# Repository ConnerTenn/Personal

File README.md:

This repository is outdated. 
Projects will now be located in their own repository and will no longer be updated here.
This repository is being kept for commit and file history.

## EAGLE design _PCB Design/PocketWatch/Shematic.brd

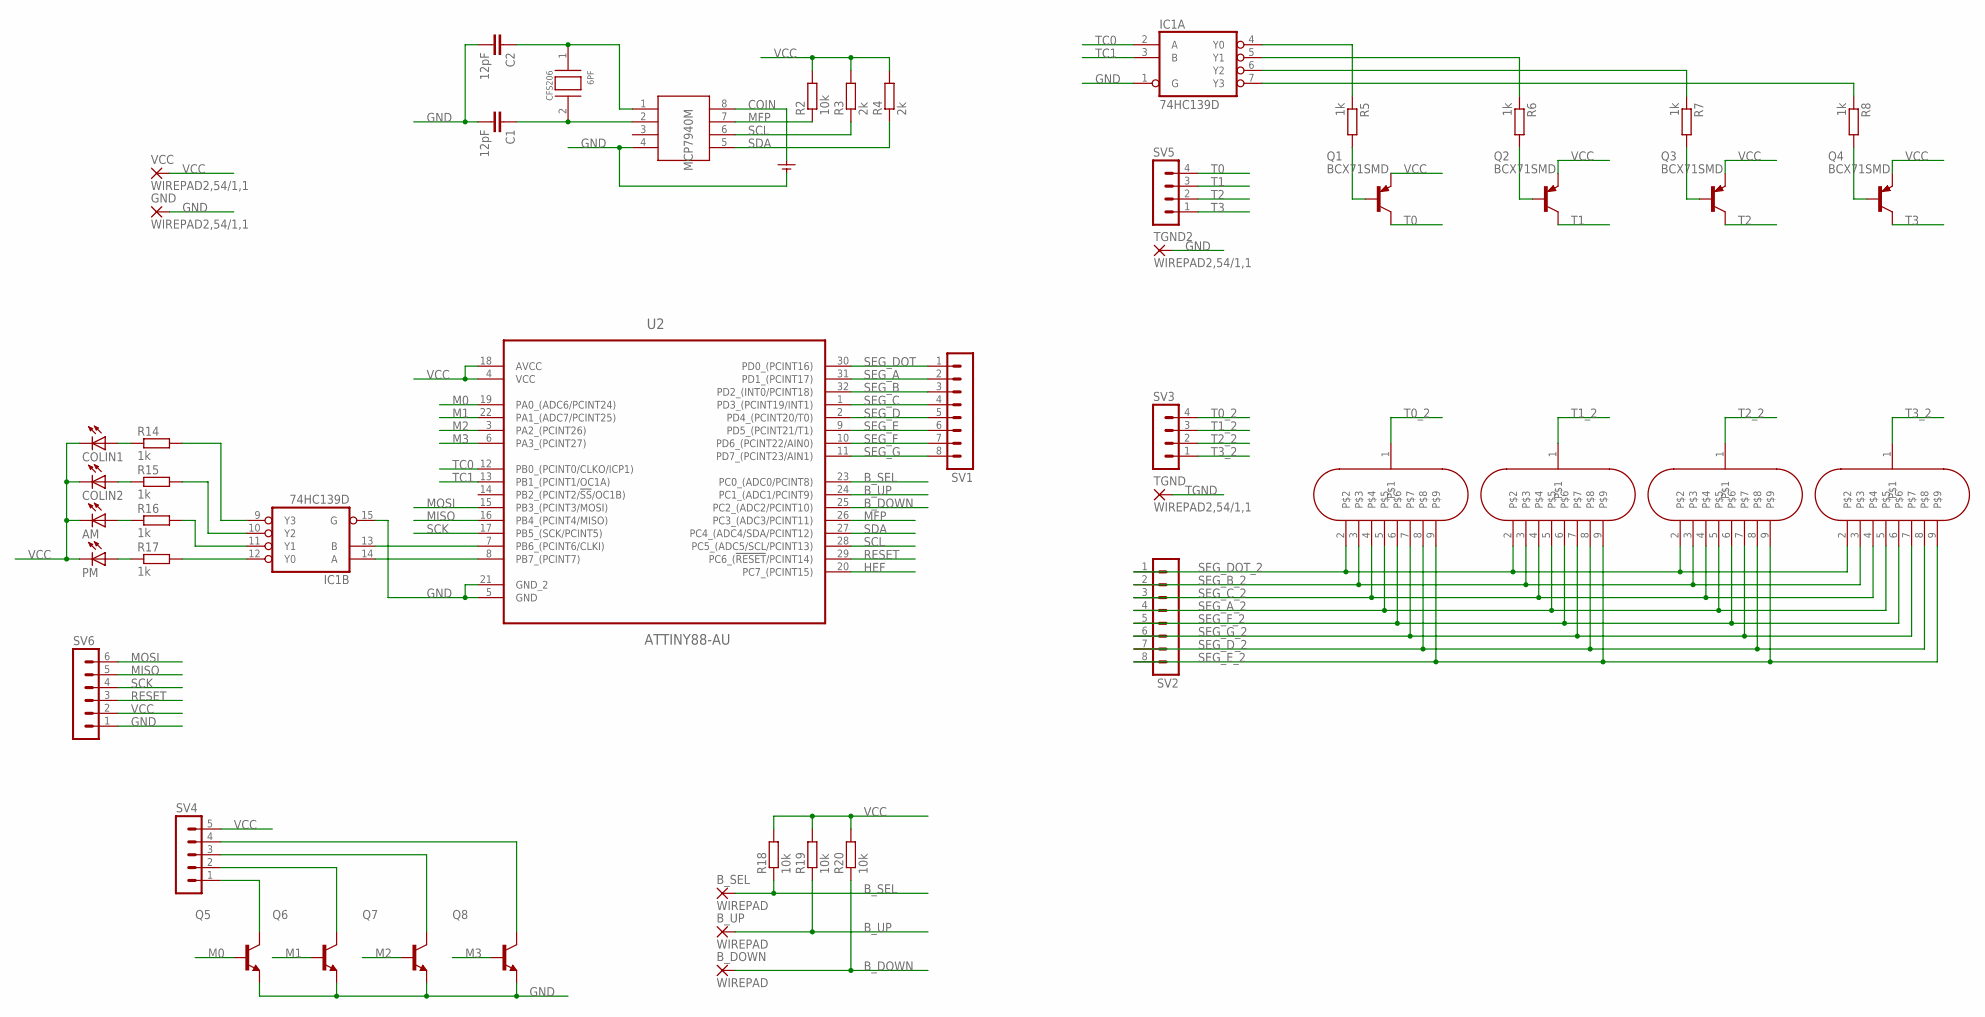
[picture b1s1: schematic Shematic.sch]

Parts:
6PF: CFS206
AM: LED_ELD260; LED_LD260
B_DOWN: WIREPAD; 2,54/1,1
B_SEL: WIREPAD; 2,54/1,1
B_UP: WIREPAD; 2,54/1,1
C1, C2: 12pF; C1206
COLIN1, COLIN2: LED_ELD260; LED_LD260
GND: WIREPAD2,54/1,1; 2,54/1,1
IC1: 74HC139D; SO16
MCP7940M: SOIC-8
PM: LED_ELD260; LED_LD260
Q1, Q2, Q3, Q4: BCX71SMD; SOT23
Q5, Q6, Q7, Q8: BCX70SMD; SOT23
R2, R18, R19, R20: 10k; R1206
R3, R4: 2k; R1206
R5, R6, R7, R8, R14, R15, R16, R17: 1k; R1206
SV1, SV2: MA08-1
SV3, SV5: MA04-1
SV4: MA05-1
SV6: MA06-1
TGND, TGND2: WIREPAD2,54/1,1; 2,54/1,1
TUBE0, TUBE1, TUBE2, TUBE3: IV-9
U2: ATTINY88-AU; QFP80P900X900X120-32N
U$5: COIN
VCC: WIREPAD2,54/1,1; 2,54/1,1

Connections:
B_DOWN: B_DOWN.1, R20.1, U2.25 (PC2_(ADC2/PCINT10))
B_SEL: B_SEL.1, R18.1, U2.23 (PC0_(ADC0/PCINT8))
B_UP: B_UP.1, R19.1, U2.24 (PC1_(ADC1/PCINT9))
COIN: MCP7940M.8, U$5.V+
GND: C1.2, C2.2, GND.1, IC1.1 (G), IC1.8 (GND), IC1.15 (G), MCP7940M.4, Q5.2 (E), Q6.2 (E), Q7.2 (E), Q8.2 (E), SV6.1, TGND2.1, U2.5 (GND), U2.21 (GND_2), U$5.V-
HEF: U2.20 (PC7_(PCINT15))
M0: Q5.1 (B), U2.19 (PA0_(ADC6/PCINT24))
M1: Q6.1 (B), U2.22 (PA1_(ADC7/PCINT25))
M2: Q7.1 (B), U2.3 (PA2_(PCINT26))
M3: Q8.1 (B), U2.6 (PA3_(PCINT27))
MFP: MCP7940M.7, R2.1, U2.26 (PC3_(ADC3/PCINT11))
MISO: SV6.5, U2.16 (PB4_(PCINT4/MISO))
MOSI: SV6.6, U2.15 (PB3_(PCINT3/MOSI))
unnamed: Q4.1 (B), R8.2
unnamed: Q3.1 (B), R7.2
unnamed: Q2.1 (B), R6.2
unnamed: 6PF.2, C1.1, MCP7940M.2
unnamed: Q1.1 (B), R5.2
unnamed: 6PF.1, C2.1, MCP7940M.1
unnamed: COLIN1.A, R14.1
unnamed: IC1.4 (Y0), R5.1
unnamed: COLIN2.A, R15.1
unnamed: IC1.5 (Y1), R6.1
unnamed: IC1.6 (Y2), R7.1
unnamed: AM.A, R16.1
unnamed: IC1.7 (Y3), R8.1
unnamed: PM.A, R17.1
unnamed: IC1.12 (Y0), R17.2
unnamed: IC1.11 (Y1), R16.2
unnamed: IC1.10 (Y2), R15.2
unnamed: IC1.9 (Y3), R14.2
unnamed: Q5.3 (C), SV4.1
unnamed: Q6.3 (C), SV4.2
unnamed: Q7.3 (C), SV4.3
unnamed: Q8.3 (C), SV4.4
unnamed: IC1.13 (B), U2.7 (PB6_(PCINT6/CLKI))
unnamed: IC1.14 (A), U2.8 (PB7_(PCINT7))
RESET: SV6.3, U2.29 (PC6_(!RESET!/PCINT14))
SCK: SV6.4, U2.17 (PB5_(SCK/PCINT5))
SCL: MCP7940M.6, R3.1, U2.28 (PC5_(ADC5/SCL/PCINT13))
SDA: MCP7940M.5, R4.1, U2.27 (PC4_(ADC4/SDA/PCINT12))
SEG_A: SV1.2, U2.31 (PD1_(PCINT17))
SEG_A_2: SV2.4, TUBE0.5, TUBE1.5, TUBE2.5, TUBE3.5
SEG_B: SV1.3, U2.32 (PD2_(INT0/PCINT18))
SEG_B_2: SV2.2, TUBE0.3, TUBE1.3, TUBE2.3, TUBE3.3
SEG_C: SV1.4, U2.1 (PD3_(PCINT19/INT1))
SEG_C_2: SV2.3, TUBE0.4, TUBE1.4, TUBE2.4, TUBE3.4
SEG_D: SV1.5, U2.2 (PD4_(PCINT20/T0))
SEG_DOT: SV1.1, U2.30 (PD0_(PCINT16))
SEG_DOT_2: SV2.1, TUBE0.2, TUBE1.2, TUBE2.2, TUBE3.2
SEG_D_2: SV2.7, TUBE0.8, TUBE1.8, TUBE2.8, TUBE3.8
SEG_E: SV1.6, U2.9 (PD5_(PCINT21/T1))
SEG_E_2: SV2.8, TUBE0.9, TUBE1.9, TUBE2.9, TUBE3.9
SEG_F: SV1.7, U2.10 (PD6_(PCINT22/AIN0))
SEG_F_2: SV2.5, TUBE0.6, TUBE1.6, TUBE2.6, TUBE3.6
SEG_G: SV1.8, U2.11 (PD7_(PCINT23/AIN1))
SEG_G_2: SV2.6, TUBE0.7, TUBE1.7, TUBE2.7, TUBE3.7
T0: Q1.3 (C), SV5.4
T0_2: SV3.4, TUBE0.1
T1: Q2.3 (C), SV5.3
T1_2: SV3.3, TUBE1.1
T2: Q3.3 (C), SV5.2
T2_2: SV3.2, TUBE2.1
T3: Q4.3 (C), SV5.1
T3_2: SV3.1, TUBE3.1
TC0: IC1.2 (A), U2.12 (PB0_(PCINT0/CLKO/ICP1))
TC1: IC1.3 (B), U2.13 (PB1_(PCINT1/OC1A))
TGND: TGND.1
VCC: AM.K (C), COLIN1.K (C), COLIN2.K (C), IC1.16 (VCC), PM.K (C), Q1.2 (E), Q2.2 (E), Q3.2 (E), Q4.2 (E), R2.2, R3.2, R4.2, R18.2, R19.2, R20.2, SV4.5, SV6.2, U2.4 (VCC), U2.18 (AVCC), VCC.1

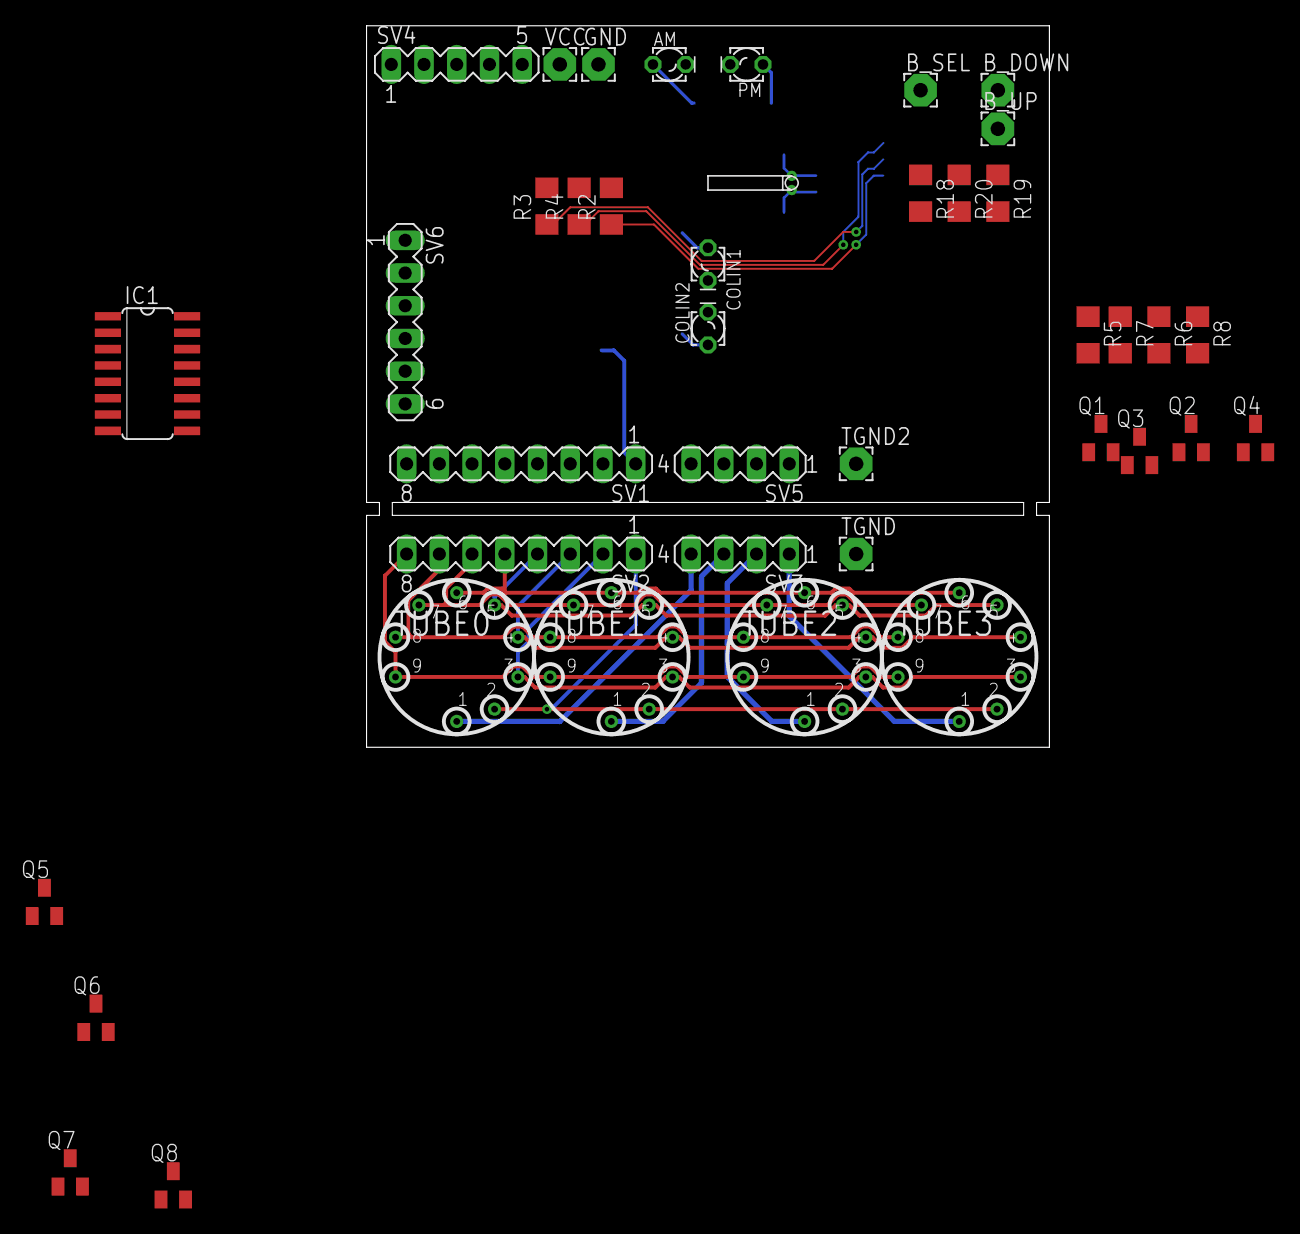
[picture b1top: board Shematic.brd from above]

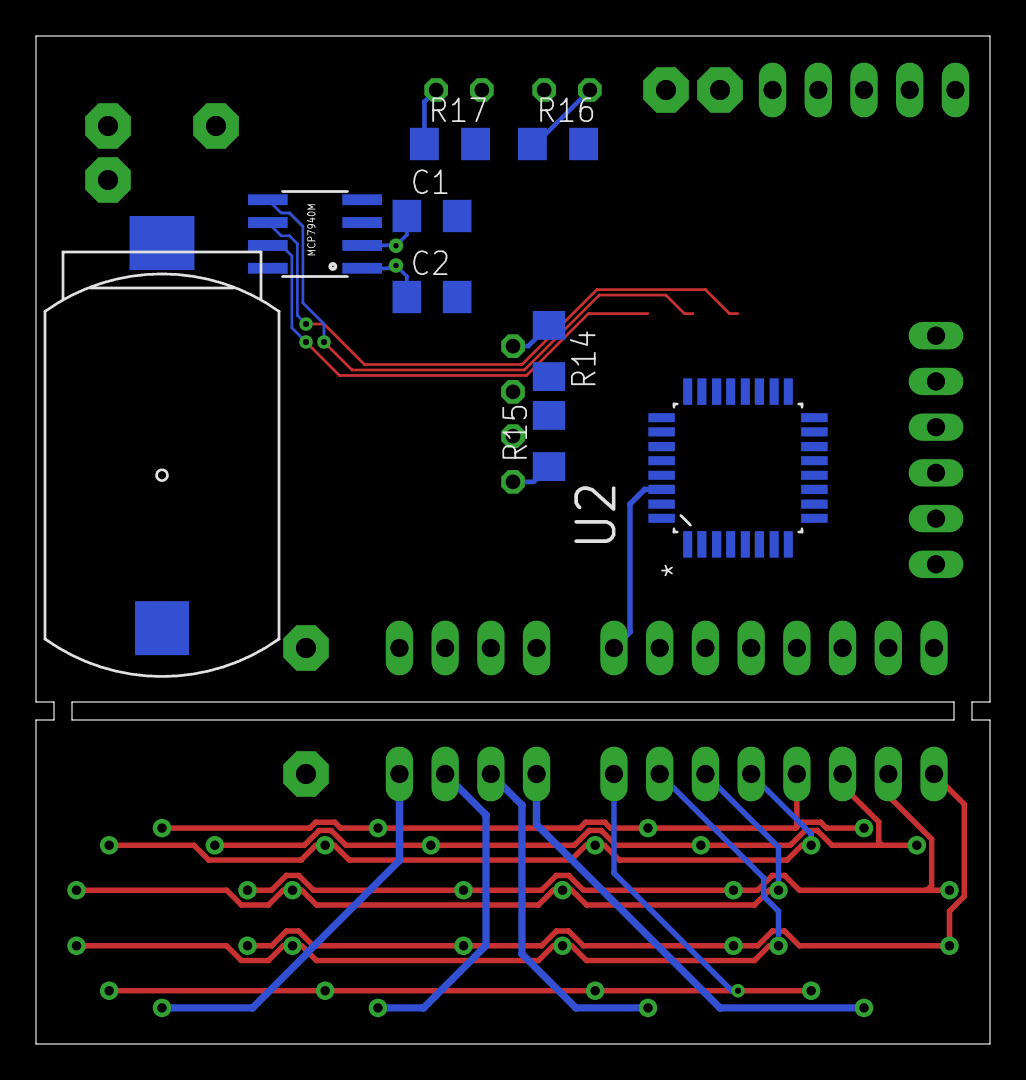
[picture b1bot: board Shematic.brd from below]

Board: 2 copper layers, 53.0 x 56.0 mm, 50 parts (9 on the bottom side), 67 nets.

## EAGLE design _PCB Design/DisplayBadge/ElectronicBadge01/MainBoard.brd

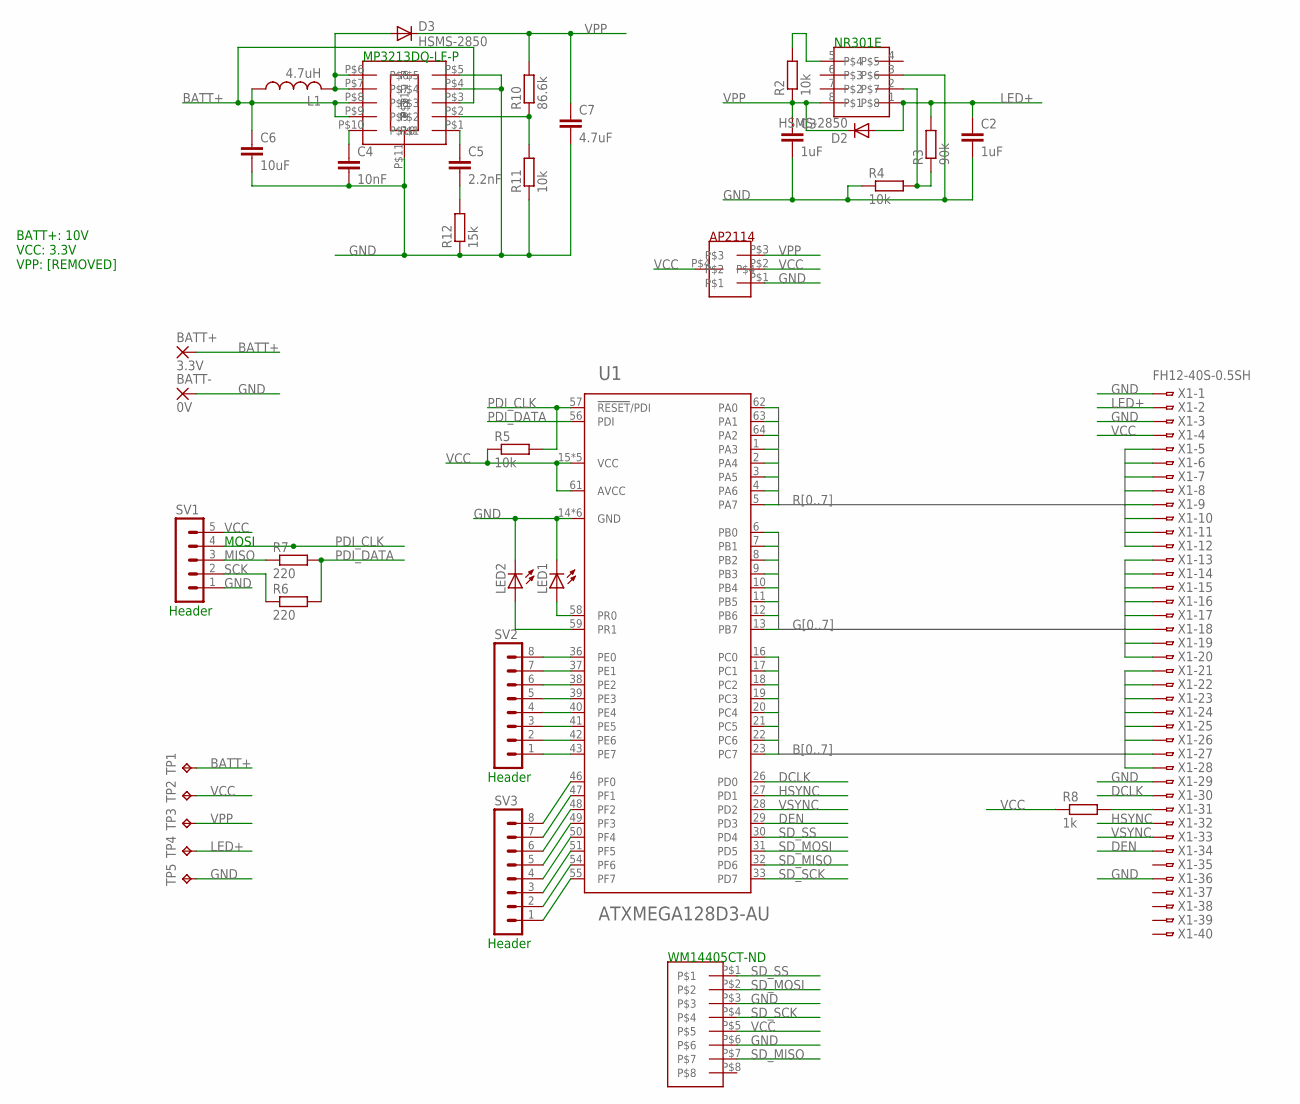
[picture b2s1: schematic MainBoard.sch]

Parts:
BATT+: 3.3V; 2,54/1,1
BATT-: 0V; 2,54/1,1
C2, C3: 1uF; C0402
C4: 10nF; C0402
C5: 2.2nF; C0402
C6: 10uF; C0402
C7: 4.7uF; C0402
D2, D3: HSMS-2850; SOT23
L1: 4.7uH; L3225M
LED1, LED2: LED_ESML0603; LED_SML0603
R2, R4, R5, R11: 10k; R0402
R3: 90k; R0402
R6, R7: 220; R0402
R8: 1k; R0402
R10: 86.6k; R0402
R12: 15k; R0402
SV1: MA05-1
SV2, SV3: MA08-1
TP1, TP2, TP3, TP4, TP5: TPPAD1-17; P1-17
U1: ATXMEGA128D3-AU; TQFP-64A-64
U$1: SOIC-8
U$2: AP2114H; SOT233
U$3: MICROSD
U$4: QFN-10
X1: FH12-40S-0.5SH

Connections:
B0: U1.16 (PC0), X1.21
B1: U1.17 (PC1), X1.22
B2: U1.18 (PC2), X1.23
B3: U1.19 (PC3), X1.24
B4: U1.20 (PC4), X1.25
B5: U1.21 (PC5), X1.26
B6: U1.22 (PC6), X1.27
B7: U1.23 (PC7), X1.28
BATT+: BATT+.1, C6.1, L1.1, TP1.TP, U$4.P$3, U$4.P$8, U$4.P$9
DCLK: U1.26 (PD0), X1.30
DEN: U1.29 (PD3), X1.34
G0: U1.6 (PB0), X1.13
G1: U1.7 (PB1), X1.14
G2: U1.8 (PB2), X1.15
G3: U1.9 (PB3), X1.16
G4: U1.10 (PB4), X1.17
G5: U1.11 (PB5), X1.18
G6: U1.12 (PB6), X1.19
G7: U1.13 (PB7), X1.20
GND: BATT-.1, C2.2, C3.2, C4.2, C6.2, C7.2, LED1.C, LED2.C, R4.1, R11.1, R12.1, SV1.1, TP5.TP, U1.14 (GND), U1.24 (GND), U1.34 (GND), U1.44 (GND), U1.52 (GND), U1.60 (GND), U$1.3, U$2.P$1, U$3.P$3, U$3.P$6, U$4.P$4, U$4.P$5, U$4.P$11, X1.1, X1.3, X1.29, X1.36
HSYNC: U1.27 (PD1), X1.32
LED+: C2.1, D2.1 (A), R3.2, TP4.TP, U$1.1, X1.2
MISO: R7.1, SV1.3
unnamed: R2.2, U$1.5
unnamed: R3.1, R4.2, U$1.2
unnamed: SV2.8, U1.36 (PE0)
unnamed: SV2.7, U1.37 (PE1)
unnamed: SV2.6, U1.38 (PE2)
unnamed: SV2.5, U1.39 (PE3)
unnamed: SV2.4, U1.40 (PE4)
unnamed: SV2.3, U1.41 (PE5)
unnamed: SV2.2, U1.42 (PE6)
unnamed: SV2.1, U1.43 (PE7)
unnamed: LED1.A, U1.58 (PR0)
unnamed: LED2.A, U1.59 (PR1)
unnamed: D3.1 (A), L1.2, U$4.P$6, U$4.P$7
unnamed: R8.2, X1.31
unnamed: SV3.8, U1.46 (PF0)
unnamed: SV3.7, U1.47 (PF1)
unnamed: SV3.6, U1.48 (PF2)
unnamed: SV3.5, U1.49 (PF3)
unnamed: SV3.4, U1.50 (PF4)
unnamed: SV3.3, U1.51 (PF5)
unnamed: SV3.2, U1.54 (PF6)
unnamed: SV3.1, U1.55 (PF7)
unnamed: C4.1, U$4.P$10
unnamed: R10.1, R11.2, U$4.P$2
unnamed: C5.1, U$4.P$1
unnamed: C5.2, R12.2
PDI_CLK: R5.2, SV1.4, U1.57 (!RESET!/PDI)
PDI_DATA: R6.2, R7.2, U1.56 (PDI)
R0: U1.62 (PA0), X1.5
R1: U1.63 (PA1), X1.6
R2: U1.64 (PA2), X1.7
R3: U1.1 (PA3), X1.8
R4: U1.2 (PA4), X1.9
R5: U1.3 (PA5), X1.10
R6: U1.4 (PA6), X1.11
R7: U1.5 (PA7), X1.12
SCK: R6.1, SV1.2
SD_MISO: U1.32 (PD6), U$3.P$7
SD_MOSI: U1.31 (PD5), U$3.P$2
SD_SCK: U1.33 (PD7), U$3.P$4
SD_SS: U1.30 (PD4), U$3.P$1
VCC: R5.1, R8.1, SV1.5, TP2.TP, U1.15 (VCC), U1.25 (VCC), U1.35 (VCC), U1.45 (VCC), U1.53 (VCC), U1.61 (AVCC), U$2.P$2, U$2.P$4, U$3.P$5, X1.4
VPP: C3.1, C7.1, D2.3 (C), D3.3 (C), R2.1, R10.2, TP3.TP, U$1.8, U$2.P$3
VSYNC: U1.28 (PD2), X1.33

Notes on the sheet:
Header
WM14405CT-ND
NR301E
MP3213DQ-LF-P
MOSI
BATT+: 10V VCC: 3.3V VPP: [REMOVED]

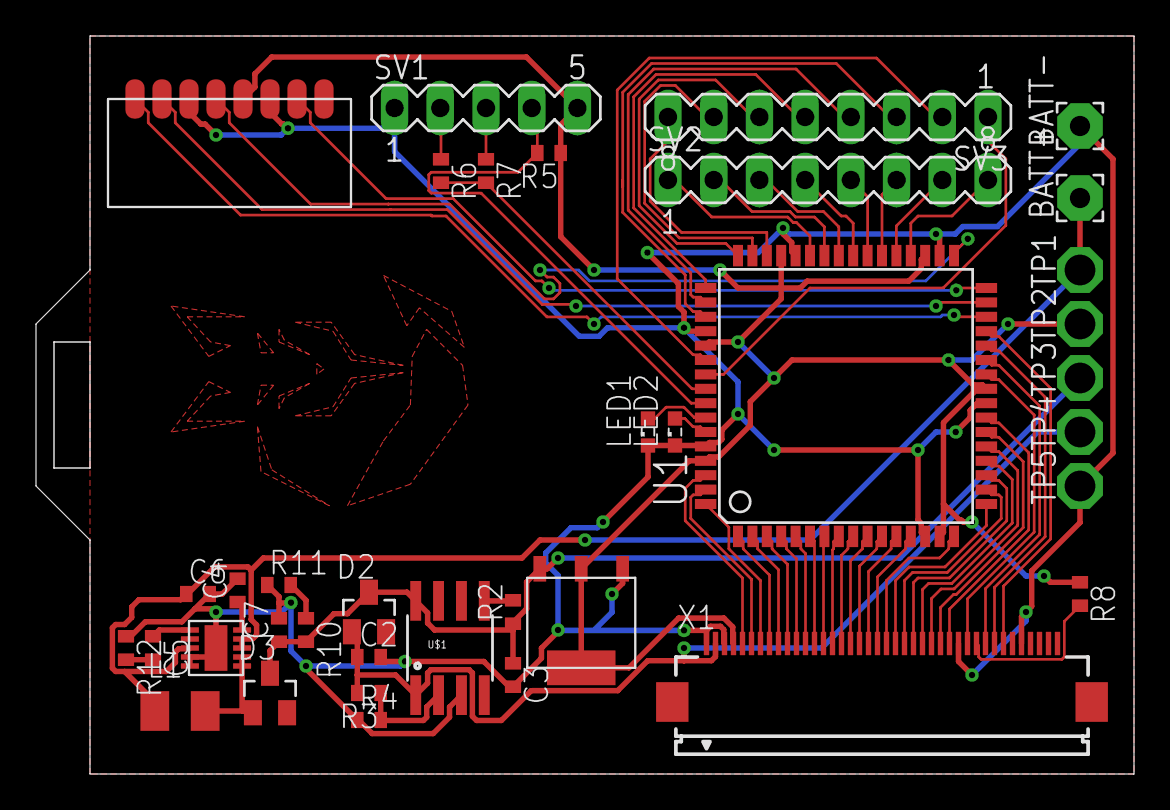
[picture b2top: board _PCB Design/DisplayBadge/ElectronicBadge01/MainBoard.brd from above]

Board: 2 copper layers, 61.0 x 41.0 mm, 37 parts (0 on the bottom side), 67 nets.

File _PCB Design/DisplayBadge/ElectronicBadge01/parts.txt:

Partlist

Exported from MainBoard.sch at 2017-10-12 2:10 AM

EAGLE Version 8.3.2 Copyright (c) 1988-2017 Autodesk, Inc.

Assembly variant: 

Part     Value          Device         Package        Library         Sheet

~ BATT+    3.3V           2,54/1,1       2,54/1,1       wirepad         1
~ BATT-    0V             2,54/1,1       2,54/1,1       wirepad         1
# C2       1uF            CC0402         C0402          eagle-ltspice   1
# C3       1uF            CC0402         C0402          eagle-ltspice   1
# C4       10nF           CC0402         C0402          eagle-ltspice   1
C5       2.2nF          CC0402         C0402          eagle-ltspice   1
# C6       10uF           CC0402         C0402          eagle-ltspice   1
# C7       4.7uF          CC0402         C0402          eagle-ltspice   1
# D2       HSMS-2850      HSMS-2850      SOT23          avago           1
# D3       HSMS-2850      HSMS-2850      SOT23          avago           1
# L1       4.7uH          L-USL3225M     L3225M         resistor        1
# LED1                    LED_ESML0603   LED_SML0603    eagle-ltspice   1
# LED2                    LED_ESML0603   LED_SML0603    eagle-ltspice   1
# R2       10k            RR0402         R0402          eagle-ltspice   1
# R3       90k            RR0402         R0402          eagle-ltspice   1
# R4       10k            RR0402         R0402          eagle-ltspice   1
# R5       10k            RR0402         R0402          eagle-ltspice   1
# R6       220            RR0402         R0402          eagle-ltspice   1
# R7       220            RR0402         R0402          eagle-ltspice   1
# R8       1k             RR0402         R0402          eagle-ltspice   1
# R10      86.6k          RR0402         R0402          eagle-ltspice   1
# R11      10k            RR0402         R0402          eagle-ltspice   1
# R12      15k            RR0402         R0402          eagle-ltspice   1
~ SV1                     MA05-1         MA05-1         con-lstb        1
~ SV2                     MA08-1         MA08-1         con-lstb        1
~ SV3                     MA08-1         MA08-1         con-lstb        1
~ TP1      TPPAD1-17      TPPAD1-17      P1-17          testpad         1
~ TP2      TPPAD1-17      TPPAD1-17      P1-17          testpad         1
~ TP3      TPPAD1-17      TPPAD1-17      P1-17          testpad         1
~ TP4      TPPAD1-17      TPPAD1-17      P1-17          testpad         1
~ TP5      TPPAD1-17      TPPAD1-17      P1-17          testpad         1
# U$1      SOIC-8         SOIC-8         SOIC-8         smd-footprints  1
# U$2      AP2114H        AP2114H        SOT233         ElectronicBadge 1
# U$3      MICROSD        MICROSD        MICROSD        ElectronicBadge 1
# U$4      QFN-10         QFN-10         QFN-10         smd-footprints  1
# U1       ATXMEGA64D3-AU ATXMEGA64D3-AU TQFP-64A-64    atmel-xmega     1
# X1       FH12-40S-0.5SH FH12-40S-0.5SH FH12-40S-0.5SH con-hirose      1

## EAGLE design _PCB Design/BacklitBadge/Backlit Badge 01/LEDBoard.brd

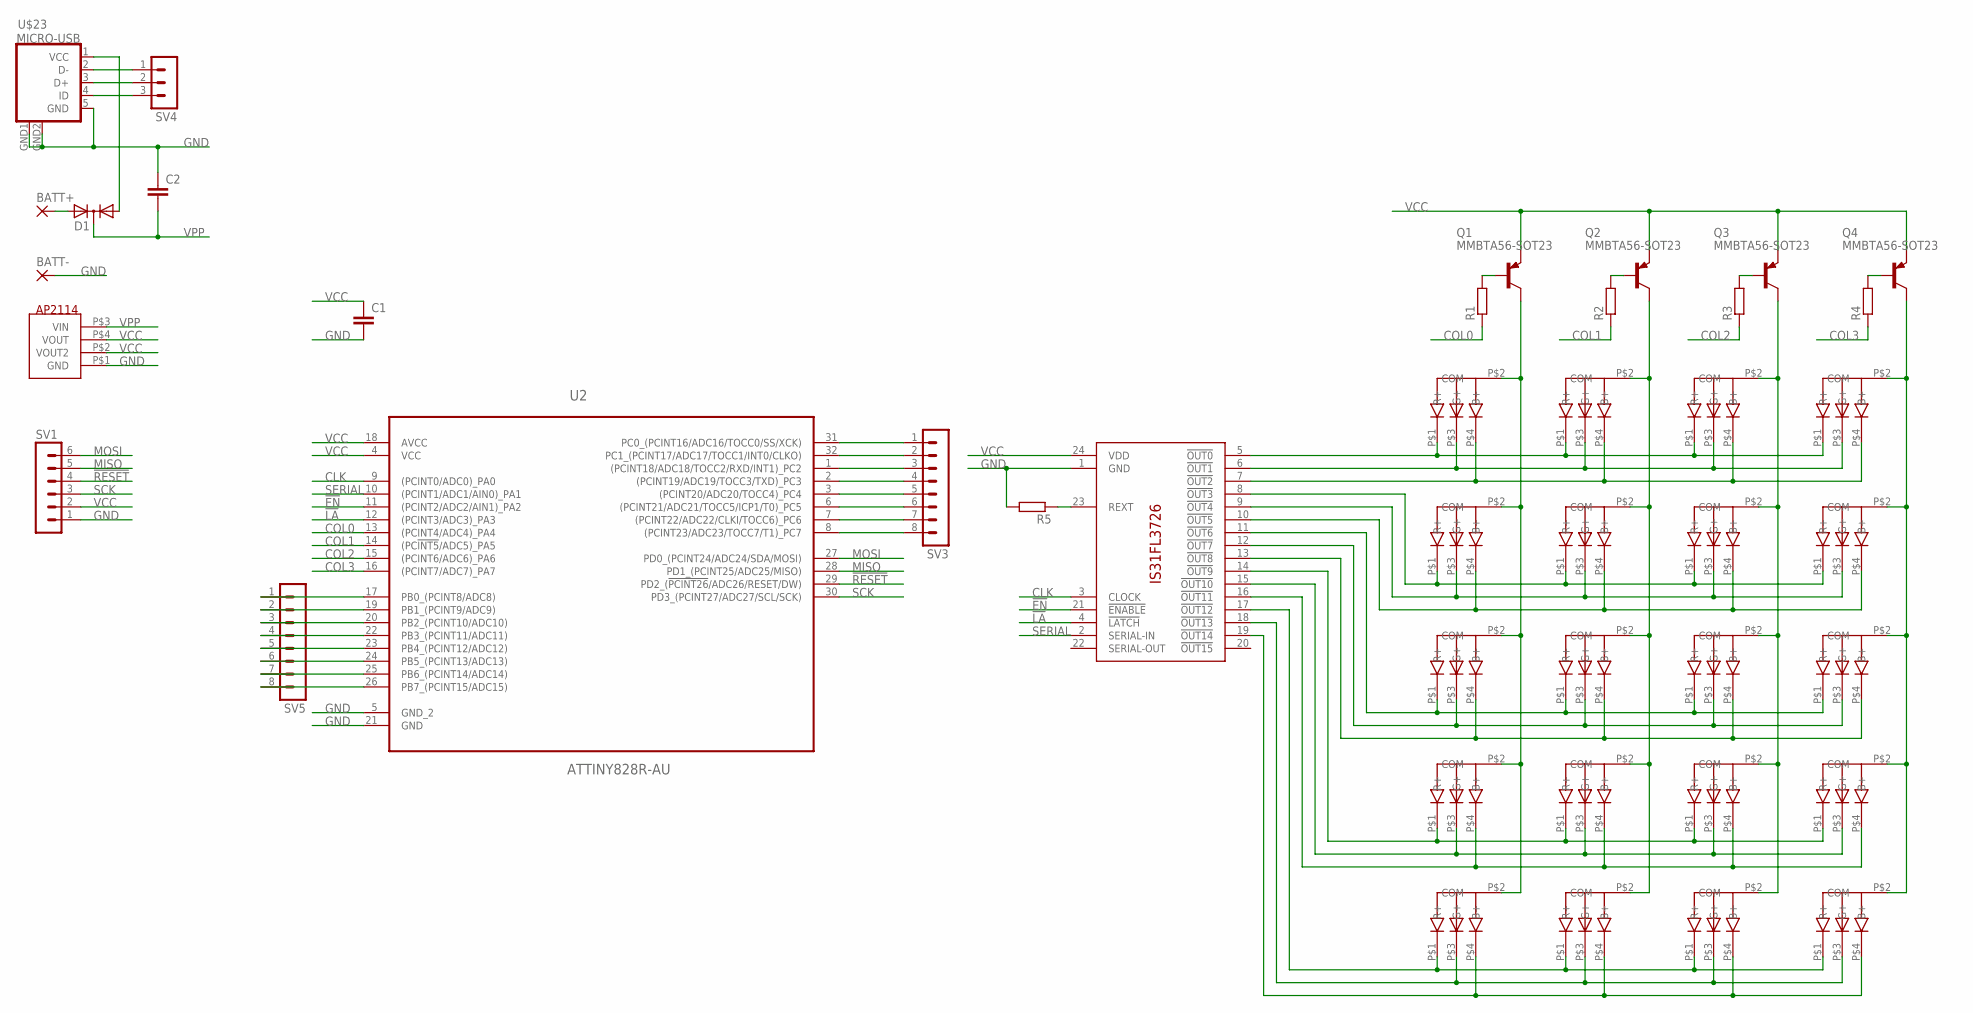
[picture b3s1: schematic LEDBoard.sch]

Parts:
BATT+: 2,54/1,1
BATT-: 2,54/1,1
C1, C2: CC1206; C1206
D1: DIODE-2AC|CASOT23; SOT23
Q1, Q2, Q3, Q4: MMBTA56-SOT23; SOT23
R1, R2, R3, R4, R5: RR1206; R1206
SV1: MA06-1
SV3, SV5: MA08-1
SV4: MA03-1
U2: ATTINY828R-AU; QFP80P900X900X120-32N
U$1: IS31FL3726; TSSOP-24
U$2: AP2114H; SOT233
U$3, U$4, U$5, U$6, U$7, U$8, U$9, U$10, U$11, U$12, U$13, U$14, U$15, U$16, U$17, U$18, U$19, U$20, U$21, U$22: 3528LED; 3528
U$23: MICRO-USB

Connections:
!EN: U2.11 ((PCINT2/ADC2/AIN1)_PA2), U$1.21 (!ENABLE)
!LA: U2.12 ((PCINT3/ADC3)_PA3), U$1.4 (!LATCH)
!RESET: SV1.4, U2.29 (PD2_(!PCINT26!/ADC26/RESET/DW))
CLK: U2.9 ((PCINT0/ADC0)_PA0), U$1.3 (CLOCK)
COL0: R1.1, U2.13 ((PCINT4/ADC4)_PA4)
COL1: R2.1, U2.14 ((PC!INT5!/ADC5)_PA5)
COL2: R3.1, U2.15 ((PCINT6/ADC6)_PA6)
COL3: R4.1, U2.16 ((PCINT7/ADC7)_PA7)
GND: BATT-.1, C1.2, C2.1, R5.2, SV1.1, U2.5 (GND_2), U2.21 (GND), U$1.1 (GND), U$2.P$1 (GND), U$23.5 (GND), U$23.GND1 (GND), U$23.GND2 (GND)
MISO: SV1.5, U2.28 (PD1_(PCINT25/ADC25/MISO))
MOSI: SV1.6, U2.27 (PD0_(PCINT24/ADC24/SDA/MOSI))
unnamed: SV3.1, U2.31 (PC0_(PCINT16/ADC16/TOCC0/SS/XCK))
unnamed: SV3.2, U2.32 (PC1_(PCINT17/ADC17/TOCC1/INT0/CLKO))
unnamed: U$1.5 (!OUT0), U$7.P$1 (R+), U$8.P$1 (R+), U$9.P$1 (R+), U$10.P$1 (R+)
unnamed: U$1.6 (!OUT1), U$7.P$3 (G+), U$8.P$3 (G+), U$9.P$3 (G+), U$10.P$3 (G+)
unnamed: U$1.7 (!OUT2), U$7.P$4 (B+), U$8.P$4 (B+), U$9.P$4 (B+), U$10.P$4 (B+)
unnamed: U$1.8 (!OUT3), U$3.P$1 (R+), U$4.P$1 (R+), U$5.P$1 (R+), U$6.P$1 (R+)
unnamed: U$1.9 (!OUT4), U$3.P$3 (G+), U$4.P$3 (G+), U$5.P$3 (G+), U$6.P$3 (G+)
unnamed: U$1.10 (!OUT5), U$3.P$4 (B+), U$4.P$4 (B+), U$5.P$4 (B+), U$6.P$4 (B+)
unnamed: U$1.11 (!OUT6), U$11.P$1 (R+), U$12.P$1 (R+), U$13.P$1 (R+), U$14.P$1 (R+)
unnamed: U$1.12 (!OUT7), U$11.P$3 (G+), U$12.P$3 (G+), U$13.P$3 (G+), U$14.P$3 (G+)
unnamed: U$1.13 (!OUT8), U$11.P$4 (B+), U$12.P$4 (B+), U$13.P$4 (B+), U$14.P$4 (B+)
unnamed: U$1.14 (!OUT9), U$15.P$1 (R+), U$16.P$1 (R+), U$17.P$1 (R+), U$18.P$1 (R+)
unnamed: U$1.15 (!OUT10), U$15.P$3 (G+), U$16.P$3 (G+), U$17.P$3 (G+), U$18.P$3 (G+)
unnamed: U$1.16 (!OUT11), U$15.P$4 (B+), U$16.P$4 (B+), U$17.P$4 (B+), U$18.P$4 (B+)
unnamed: U$1.17 (!OUT12), U$19.P$1 (R+), U$20.P$1 (R+), U$21.P$1 (R+), U$22.P$1 (R+)
unnamed: U$1.18 (!OUT13), U$19.P$3 (G+), U$20.P$3 (G+), U$21.P$3 (G+), U$22.P$3 (G+)
unnamed: U$1.19 (!OUT14), U$19.P$4 (B+), U$20.P$4 (B+), U$21.P$4 (B+), U$22.P$4 (B+)
unnamed: Q1.3 (C), U$3.P$2 (COM), U$7.P$2 (COM), U$11.P$2 (COM), U$15.P$2 (COM), U$22.P$2 (COM)
unnamed: Q2.3 (C), U$4.P$2 (COM), U$8.P$2 (COM), U$12.P$2 (COM), U$16.P$2 (COM), U$21.P$2 (COM)
unnamed: Q3.3 (C), U$5.P$2 (COM), U$9.P$2 (COM), U$13.P$2 (COM), U$17.P$2 (COM), U$20.P$2 (COM)
unnamed: Q4.3 (C), U$6.P$2 (COM), U$10.P$2 (COM), U$14.P$2 (COM), U$18.P$2 (COM), U$19.P$2 (COM)
unnamed: Q1.1 (B), R1.2
unnamed: Q2.1 (B), R2.2
unnamed: Q3.1 (B), R3.2
unnamed: Q4.1 (B), R4.2
unnamed: R5.1, U$1.23 (REXT)
unnamed: SV3.3, U2.1 ((PCINT18/ADC18/TOCC2/RXD/INT1)_PC2)
unnamed: SV3.4, U2.2 ((PCINT19/ADC19/TOCC3/TXD)_PC3)
unnamed: SV3.5, U2.3 ((PCINT20/ADC20/TOCC4)_PC4)
unnamed: SV3.6, U2.6 ((PCINT21/ADC21/TOCC5/ICP1/T0)_PC5)
unnamed: SV3.7, U2.7 ((PCINT22/ADC22/CLKI/TOCC6)_PC6)
unnamed: SV3.8, U2.8 ((PCINT23/ADC23/TOCC7/T1)_PC7)
unnamed: SV5.1, U2.17 (PB0_(PCINT8/ADC8))
unnamed: SV5.2, U2.19 (PB1_(PCINT9/ADC9))
unnamed: SV5.3, U2.20 (PB2_(PCINT10/ADC10))
unnamed: SV5.4, U2.22 (PB3_(PCINT11/ADC11))
unnamed: SV5.5, U2.23 (PB4_(PCINT12/ADC12))
unnamed: SV5.6, U2.24 (PB5_(PCINT13/ADC13))
unnamed: SV5.7, U2.25 (PB6_(PCINT14/ADC14))
unnamed: SV5.8, U2.26 (PB7_(PCINT15/ADC15))
unnamed: SV4.1, U$23.2 (D-)
unnamed: D1.1 (A1), U$23.1 (VCC)
unnamed: SV4.2, U$23.3 (D+)
unnamed: BATT+.1, D1.2 (A2)
unnamed: SV4.3, U$23.4 (ID)
SCK: SV1.3, U2.30 (PD3_(PCINT27/ADC27/SCL/SCK))
SERIAL: U2.10 ((PCINT1/ADC1/AIN0)_PA1), U$1.2 (SERIAL-IN)
VCC: C1.1, Q1.2 (E), Q2.2 (E), Q3.2 (E), Q4.2 (E), SV1.2, U2.4 (VCC), U2.18 (AVCC), U$1.24 (VDD), U$2.P$2 (VOUT2), U$2.P$4 (VOUT)
VPP: C2.2, D1.3 (C), U$2.P$3 (VIN)

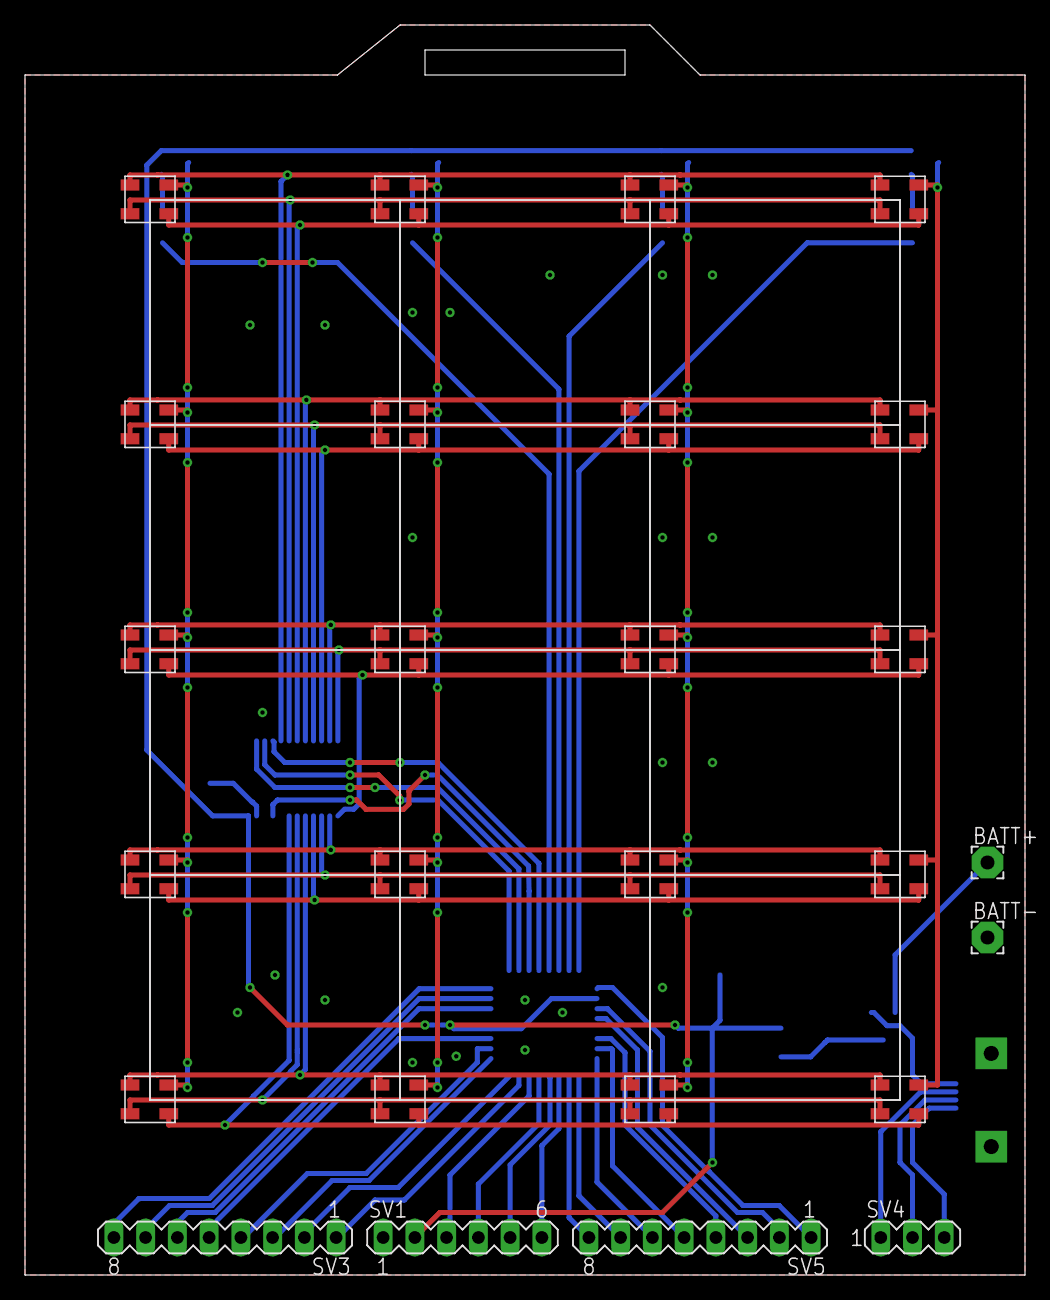
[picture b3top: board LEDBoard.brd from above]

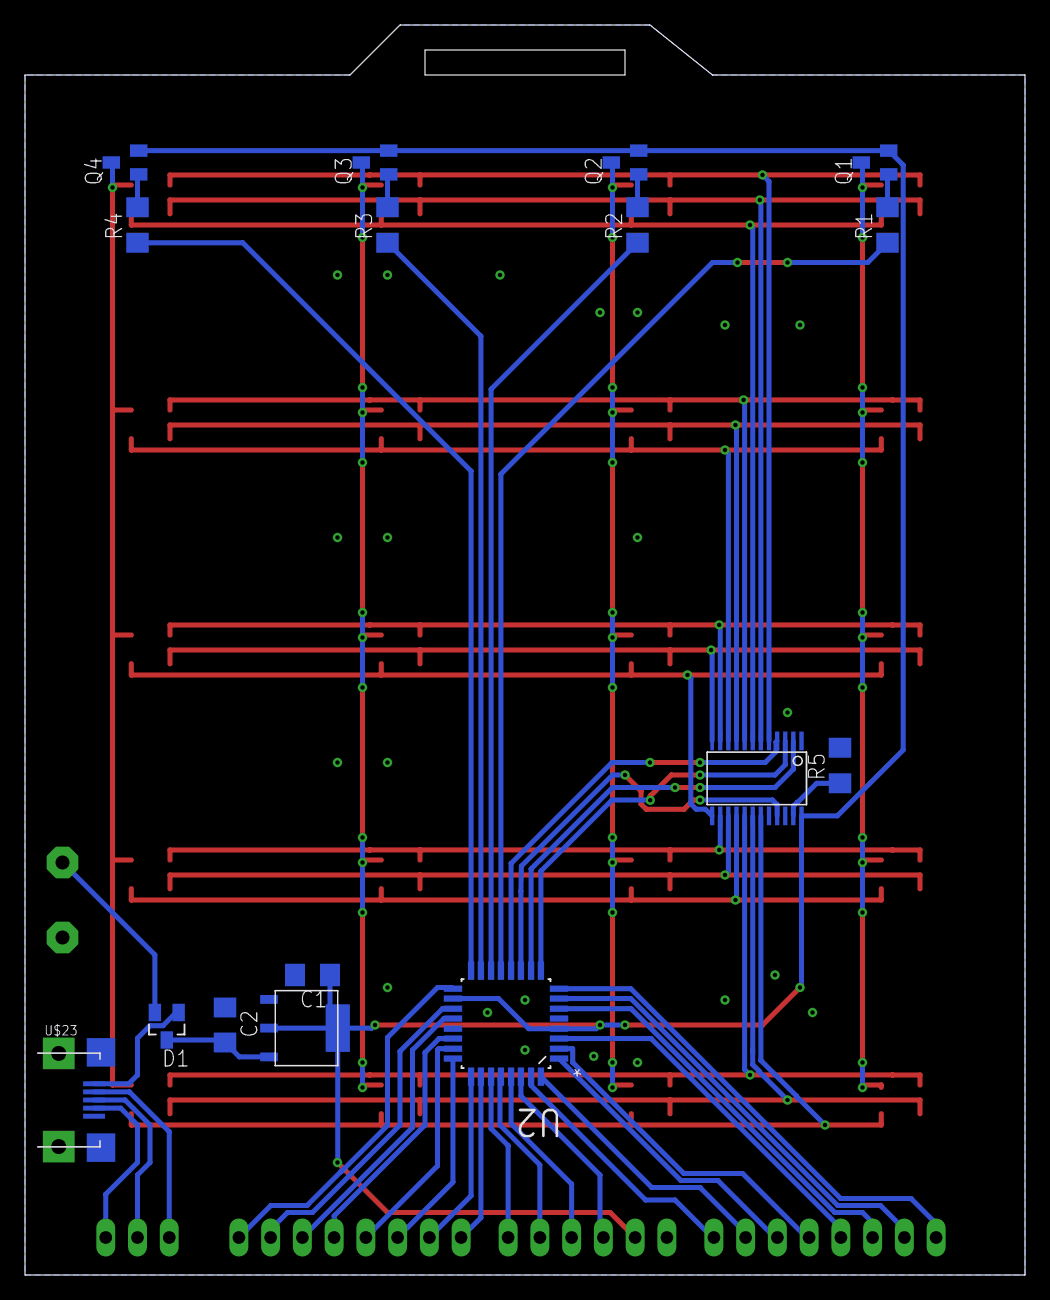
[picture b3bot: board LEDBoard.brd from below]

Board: 2 copper layers, 80.0 x 100.0 mm, 42 parts (16 on the bottom side), 60 nets.
